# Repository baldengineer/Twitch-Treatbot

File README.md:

A modified candy dispenser. It connects to Twitch's API using an Adafruit Feather Huzzah. Actions in chat delivers treats to the streamer.

Version 2? was on protoboard but has some power issues.

Version 3 (current) is a carrier for a feather that drives a stepper motor.

## Bald Engineer Live Stream
You can watch this project live (or archived) at https://twitch.tv/baldengineer

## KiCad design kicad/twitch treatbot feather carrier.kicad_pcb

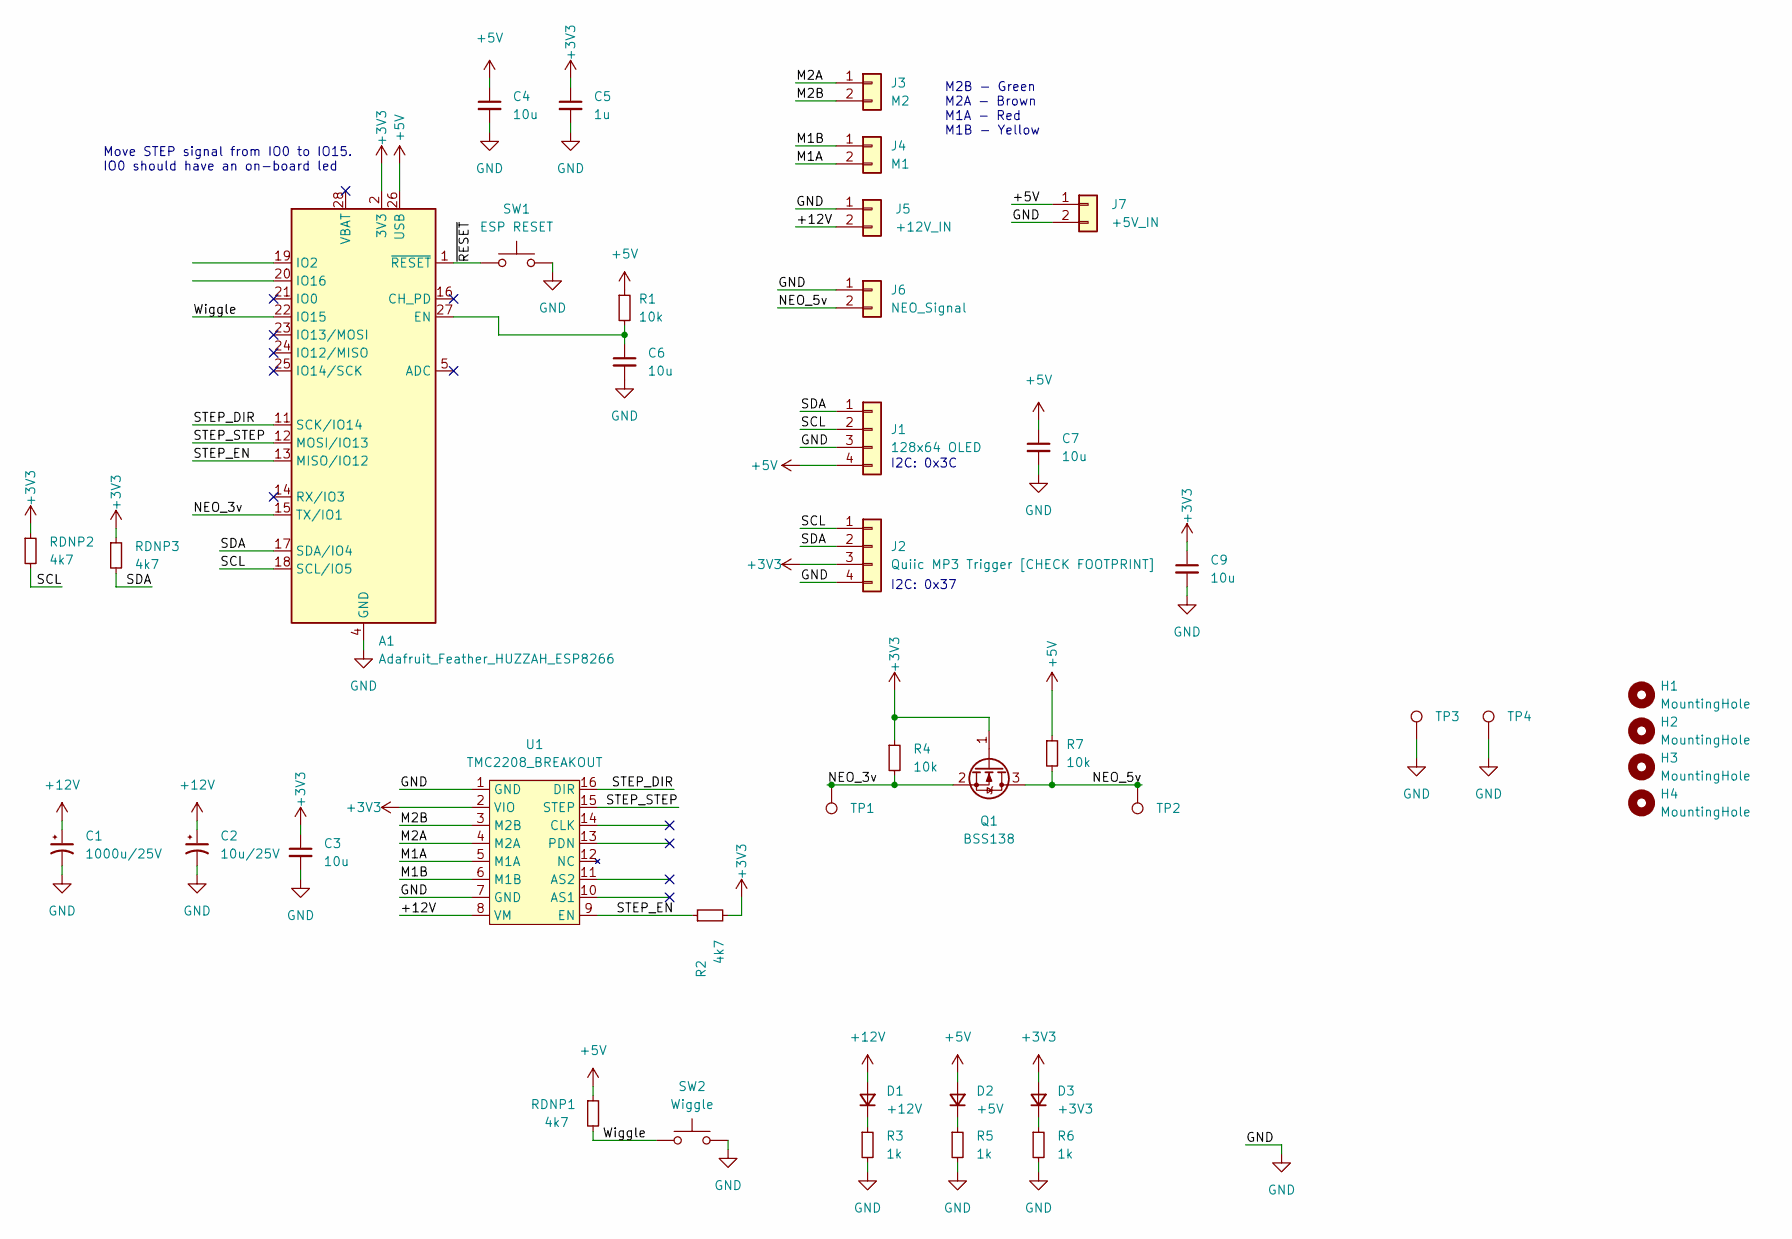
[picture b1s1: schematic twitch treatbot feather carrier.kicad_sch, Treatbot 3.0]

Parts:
A1: Adafruit_Feather_HUZZAH_ESP8266; Adafruit_Feather
C1: 1000u/25V; CP_Radial_D13.0mm_P5.00mm
C2: 10u/25V; CP_Radial_D8.0mm_P3.80mm
C3, C4, C6, C7, C9: 10u; C_0805_2012Metric
C5: 1u; C_0805_2012Metric
D1: +12V; LED_1206_3216Metric
D2: +5V; LED_1206_3216Metric
D3: +3V3; LED_1206_3216Metric
H1, H2, H3, H4: MountingHole; MountingHole_2.2mm_M2
J1: 128x64 OLED; PinSocket_1x04_P2.54mm_Vertical
J2: Quiic MP3 Trigger [CHECK FOOTPRINT]; PinSocket_1x04_P2.54mm_Vertical
J3: M2; TerminalBlock_Altech_AK300-2_P5.00mm
J4: M1; TerminalBlock_Altech_AK300-2_P5.00mm
J5: +12V_IN; TerminalBlock_Altech_AK300-2_P5.00mm
J6: NEO_Signal; TerminalBlock_Altech_AK300-2_P5.00mm
J7: +5V_IN; PinHeader_1x02_P2.54mm_Vertical
Q1: BSS138; SOT-23
R1, R4, R7: 10k; R_0805_2012Metric
R2: 4k7; R_0805_2012Metric
R3, R5, R6: 1k; R_0805_2012Metric
RDNP1, RDNP2, RDNP3: 4k7; R_0805_2012Metric
SW1: ESP RESET; SW_Push_CK_PTS525_SM15
SW2: Wiggle; SW_Push_CK_PTS525_SM15
TP1, TP2, TP3, TP4: TestPoint_Harwin; Harwin-S1751-46-Test-Point
U1: TMC2208_BREAKOUT; DIP-16_W12.7mm

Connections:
+3V3: A1.2 (3V3), C3.1, C5.1, C9.1, D3.2 (A), J2.3, Q1.1 (G), R2.2, R4.1, RDNP2.1, RDNP3.1, U1.2 (VIO)
+5V: A1.26 (USB), C4.1, C7.1, D2.2 (A), J1.4, J7.1, R1.1, R7.1, RDNP1.1
+12V: C1.1, C2.1, D1.2 (A), J5.2, U1.8 (VM)
/M1A: J4.2, U1.5 (M1A)
/M1B: J4.1, U1.6 (M1B)
/M2A: J3.1, U1.4 (M2A)
/M2B: J3.2, U1.3 (M2B)
/NEO_3v: A1.15 (TX/IO1), Q1.2 (S), R4.2, TP1.1
/NEO_5v: J6.2, Q1.3 (D), R7.2, TP2.1
/SCL: A1.18 (SCL/IO5), J1.2, J2.1, RDNP2.2
/SDA: A1.17 (SDA/IO4), J1.1, J2.2, RDNP3.2
/STEP_DIR: A1.11 (SCK/IO14), U1.16 (DIR)
/STEP_EN: A1.13 (MISO/IO12), R2.1, U1.9 (EN)
/STEP_STEP: A1.12 (MOSI/IO13), U1.15 (STEP)
/Wiggle: A1.22 (IO15), RDNP1.2, SW2.1
/~RESET: A1.1 (~RESET), SW1.1
GND: A1.4 (GND), C1.2, C2.2, C3.2, C4.2, C5.2, C6.2, C7.2, C9.2, J1.3, J2.4, J5.1, J6.1, J7.2, R3.2, R5.2, R6.2, SW1.2, SW2.2, TP3.1, TP4.1, U1.1 (GND), U1.7 (GND)
unnamed: A1.27 (EN), C6.1, R1.2
unnamed: D1.1 (K), R3.1
unnamed: D2.1 (K), R5.1
unnamed: D3.1 (K), R6.1

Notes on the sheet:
Move STEP signal from IO0 to IO15. IO0 should have an on-board led
I2C: 0x37
I2C: 0x3C
M2B - Green M2A - Brown M1A - Red M1B - Yellow

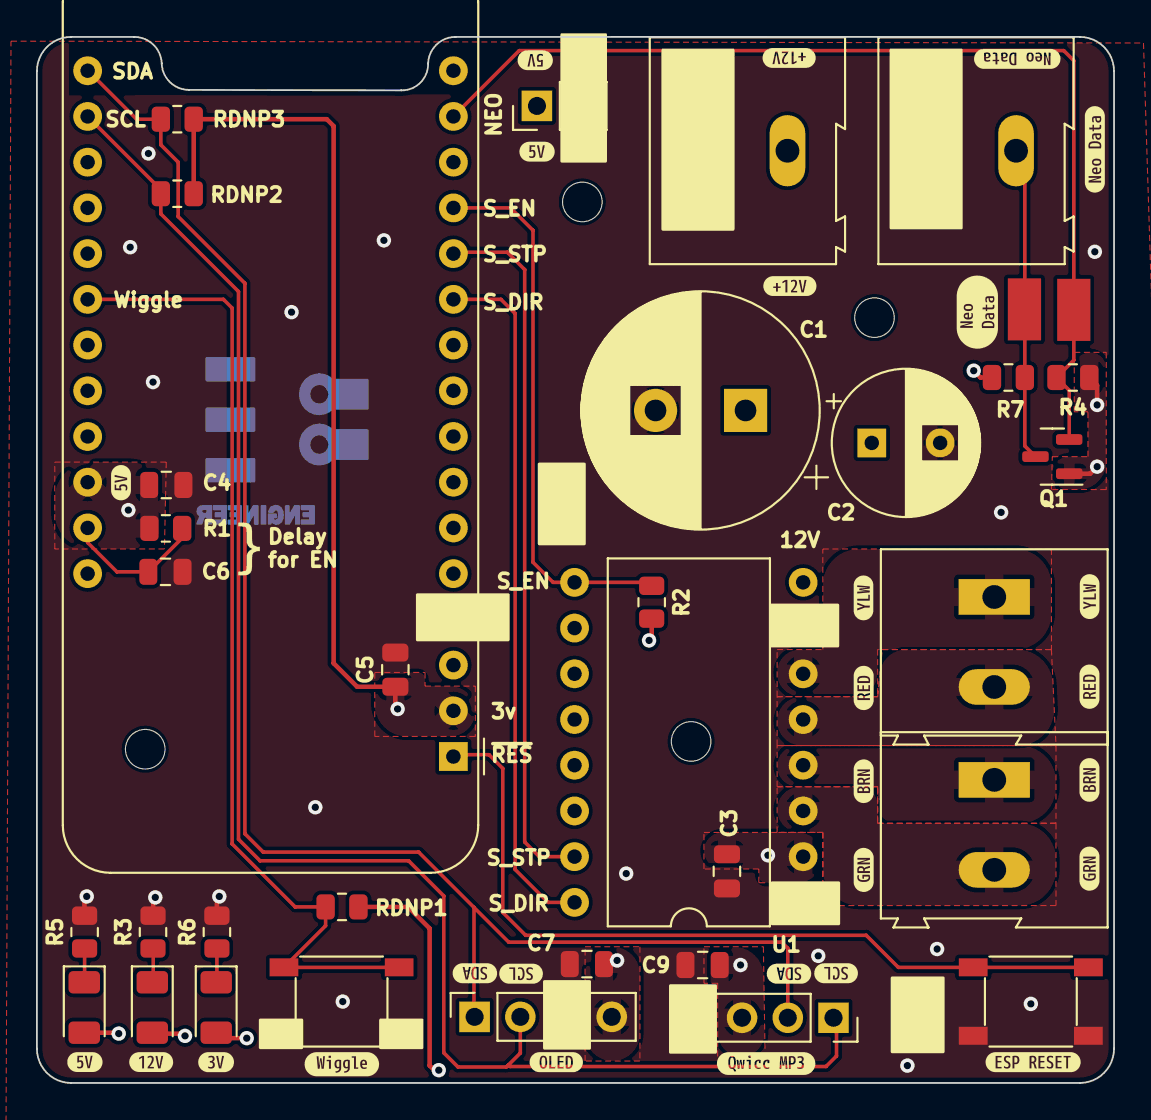
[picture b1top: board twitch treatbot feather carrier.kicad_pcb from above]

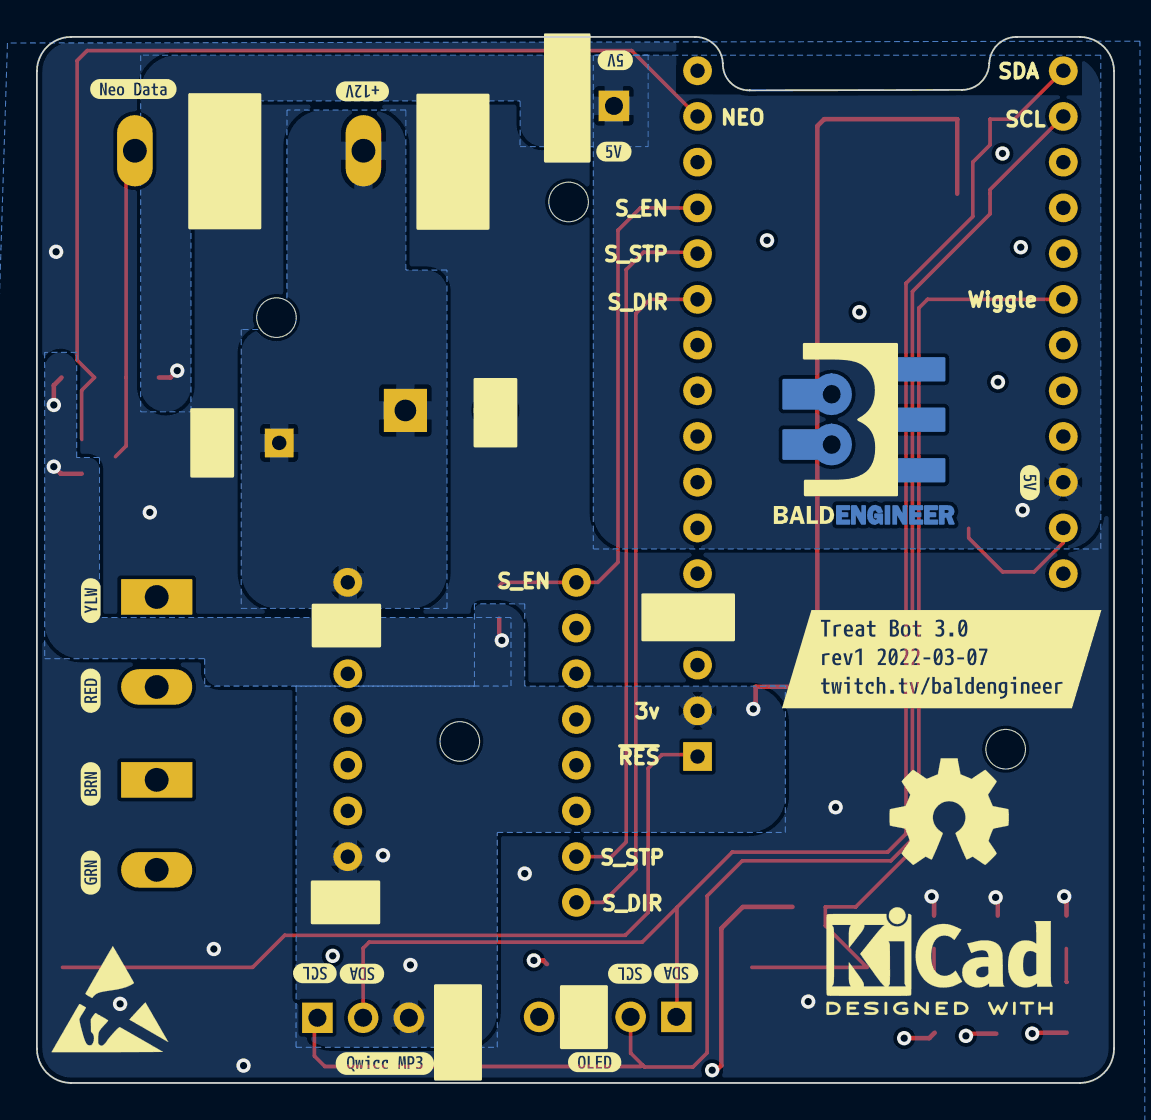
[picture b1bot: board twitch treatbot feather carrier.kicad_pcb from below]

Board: 4 copper layers, 59.8 x 58.1 mm, 86 parts (17 on the bottom side), 21 nets.

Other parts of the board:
kibuzzard-622632CA: G***; kibuzzard-622632CA
kibuzzard-622632E6: G***; kibuzzard-622632E6
kibuzzard-622632F0, kibuzzard-622632F0#2, kibuzzard-622632F0#3: G***; kibuzzard-622632F0
kibuzzard-622632F9: G***; kibuzzard-622632F9
kibuzzard-622633E5, kibuzzard-622633E5#2, kibuzzard-622633E5#3: G***; kibuzzard-622633E5
kibuzzard-622633FA, kibuzzard-622633FA#2, kibuzzard-622633FA#3: G***; kibuzzard-622633FA
kibuzzard-622634A8, kibuzzard-622634A8#2, kibuzzard-622634A8#3, kibuzzard-622634A8#4: G***; kibuzzard-622634A8
kibuzzard-622642D3: G***; kibuzzard-622642D3
kibuzzard-622647CC: G***; kibuzzard-622647CC
kibuzzard-6226330D, kibuzzard-6226330D#2: G***; kibuzzard-6226330D
kibuzzard-6226331D, kibuzzard-6226331D#2: G***; kibuzzard-6226331D
kibuzzard-62263363: G***; kibuzzard-62263363
kibuzzard-62263378, kibuzzard-62263378#2, kibuzzard-62263378#3, kibuzzard-62263378#4: G***; kibuzzard-62263378
kibuzzard-62263388, kibuzzard-62263388#2, kibuzzard-62263388#3, kibuzzard-62263388#4: G***; kibuzzard-62263388
kibuzzard-62263418, kibuzzard-62263418#2, kibuzzard-62263418#3: G***; kibuzzard-62263418
kibuzzard-62263431, kibuzzard-62263431#2, kibuzzard-62263431#3: G***; kibuzzard-62263431
kibuzzard-62263473: G***; kibuzzard-62263473
kibuzzard-62263481, kibuzzard-62263481#2, kibuzzard-62263481#3: G***; kibuzzard-62263481
kibuzzard-62263491, kibuzzard-62263491#2, kibuzzard-62263491#3: G***; kibuzzard-62263491
svg2mod: G***; BE10v2

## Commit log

2022-03-06 version 2 code without AIO keys heh!
2022-03-06 adding v2 enclosure -- probably won't change any for version 3
2022-03-06 added link to dispnser
2022-03-06 blank kicad commit, ignore *.zip because of backups
2022-03-07 PCB floorplanning
2022-03-07 first floorplan done
2022-03-07 2nd floorplan
2022-03-07 Layout done, fully routed, most of silk done, debating if to convert to 2 layer board
2022-03-07 forgot mounting holes!
2022-03-07 rev1-to-fab
2022-03-29 added extra files post-fab and pre-ibom
2022-03-29 ibom for stream and bald pnp to go brrrr
2022-12-04 added NC to existing pins and made notes after reviewing built design. IO15 was a lousy pick for the Wiggle button.
2022-12-04 updated pinouts for new control board. added more status updates to OLED. stepper driver not yet tested.
2022-12-04 minor clean up (compile status not checked)
2022-12-05 fixed WDT reboot (and adjusted values for hershey kisses)
2022-12-05 removed fast LED because it spams the serial port
2022-12-05 pio initial commit
2022-12-05 sample config file
2022-12-05 testing multiple definition issue
2022-12-05 esp32 connects to mqtt with SSL and blinks a LED
2022-12-05 ignore my cert changes
2022-12-05 ignore this file ...
2022-12-06 added some stepper stuff
2022-12-06 added oled and cleaned up stat messaging
2022-12-06 Candy graphic test...
2022-12-06 moar noise maker stuff
2022-12-09 reworked serial wait to include a character
2022-12-09 made comment less confusing
2022-12-09 dispensing on esp32 working
2022-12-09 added Pixel Panel - Yay!
2022-12-09 added noises and got treats
2022-12-09 laptop config
2022-12-09 removing obsolete code
2023-01-26 updated gears for slightly better fit
